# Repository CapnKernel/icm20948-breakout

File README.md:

# icm20948-breakout
A PCB done in KiCad to break out an ICM20948 IMU

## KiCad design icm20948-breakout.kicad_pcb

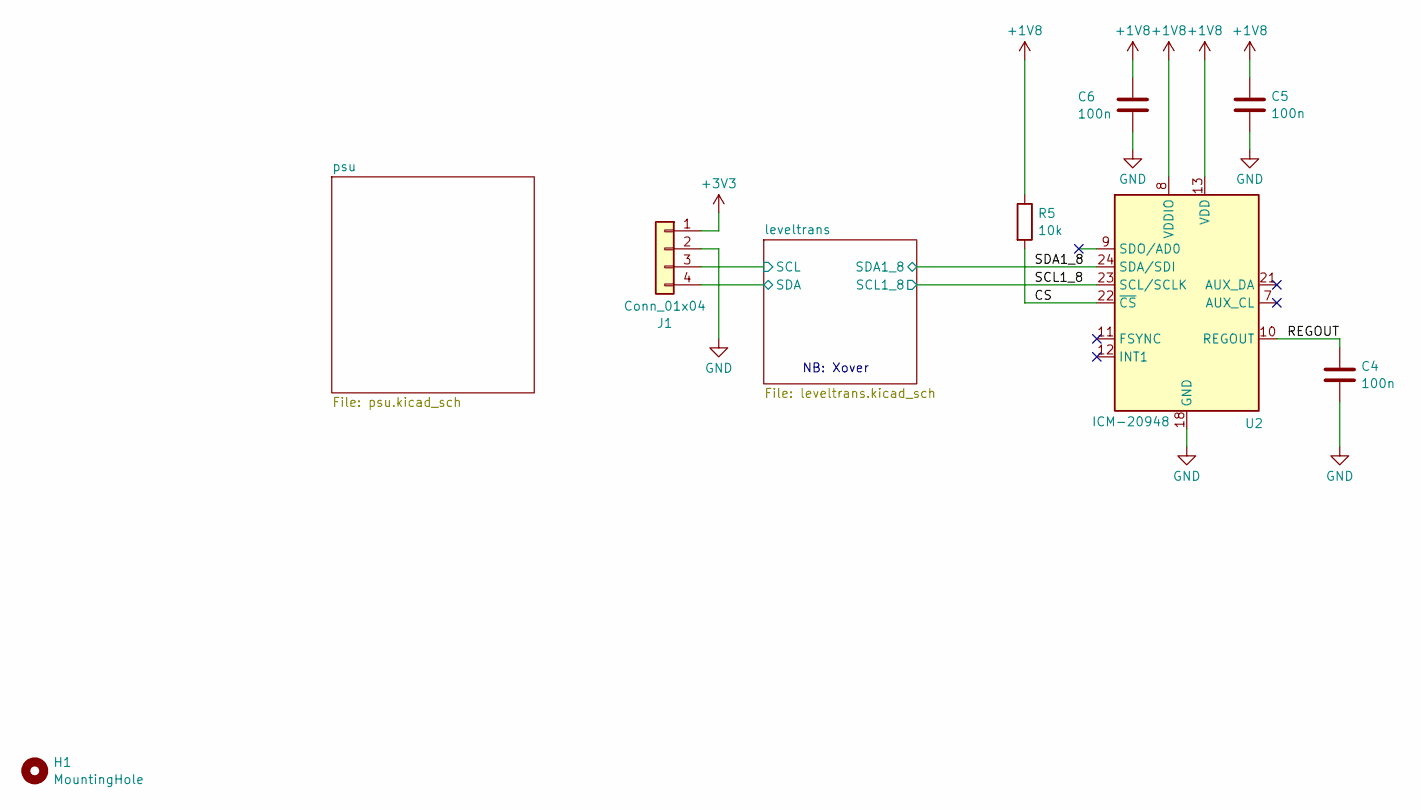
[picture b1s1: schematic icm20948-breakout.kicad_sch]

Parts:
C4, C5, C6: 100n; C_0402_1005Metric_Pad0.74x0.62mm_HandSolder; LCSC C1525
H1: MountingHole; MountingHole_2.2mm_M2
J1: Conn_01x04; PinHeader_1x04_P2.54mm_Vertical
R5: 10k; R_0402_1005Metric_Pad0.72x0.64mm_HandSolder; LCSC C25744
U2: ICM-20948; InvenSense_QFN-24_3x3mm_P0.4mm; LCSC C726001

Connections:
+1V8: C5.1, C6.1, R5.1, U2.8 (VDDIO), U2.13 (VDD); also elsewhere on the board
+3V3: J1.1; also elsewhere on the board
/CS: R5.2, U2.22 (~CS)
/REGOUT: C4.1, U2.10 (REGOUT)
/SCL1_8: U2.23 (SCL/SCLK); also elsewhere on the board
/SDA1_8: U2.24 (SDA/SDI); also elsewhere on the board
/leveltrans/SCL: J1.3; also elsewhere on the board
/leveltrans/SDA: J1.4; also elsewhere on the board
GND: C4.2, C5.2, C6.2, J1.2, U2.18 (GND), U2.20 (GND); also elsewhere on the board

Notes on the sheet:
NB: Xover

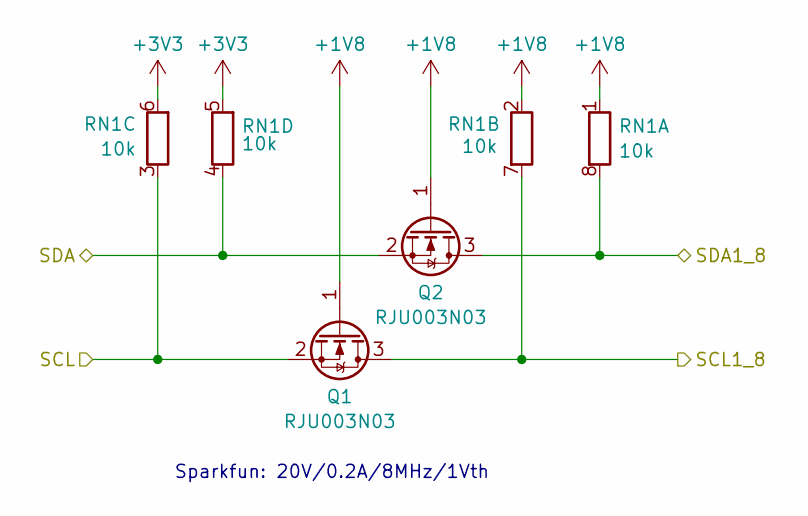
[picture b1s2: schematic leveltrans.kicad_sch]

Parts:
Q1, Q2: RJU003N03; SOT-323_SC-70_Handsoldering; LCSC C308741
RN1: 10k; R_Array_Convex_4x0603; LCSC C29718

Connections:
+1V8: Q1.1 (G), Q2.1 (G), RN1.1 (R1.1), RN1.2 (R2.1); also elsewhere on the board
+3V3: RN1.5 (R4.2), RN1.6 (R3.2); also elsewhere on the board
/SCL1_8: Q1.3 (D), RN1.7 (R2.2); also elsewhere on the board
/SDA1_8: Q2.3 (D), RN1.8 (R1.2); also elsewhere on the board
/leveltrans/SCL: Q1.2 (S), RN1.3 (R3.1); also elsewhere on the board
/leveltrans/SDA: Q2.2 (S), RN1.4 (R4.1); also elsewhere on the board

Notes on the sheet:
Sparkfun: 20V/0.2A/8MHz/1Vth

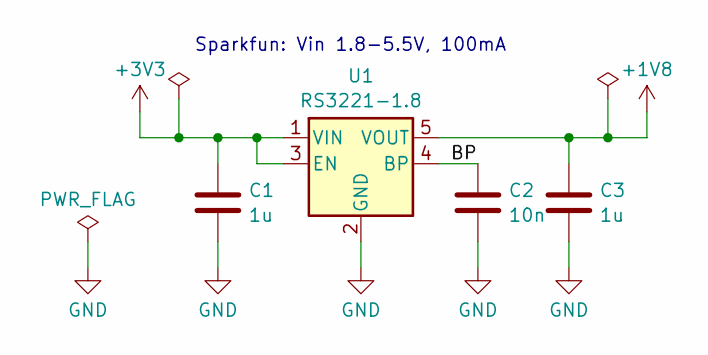
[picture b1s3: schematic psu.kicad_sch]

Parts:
C1, C3: 1u; C_0402_1005Metric_Pad0.74x0.62mm_HandSolder; LCSC C52923
C2: 10n; C_0402_1005Metric_Pad0.74x0.62mm_HandSolder; LCSC C15195
U1: RS3221-1.8; SOT-23-5; LCSC C2762317

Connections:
+1V8: C3.1, U1.5 (VOUT); also elsewhere on the board
+3V3: C1.1, U1.1 (VIN), U1.3 (EN); also elsewhere on the board
/psu/BP: C2.1, U1.4 (BP)
GND: C1.2, C2.2, C3.2, U1.2 (GND); also elsewhere on the board

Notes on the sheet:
Sparkfun: Vin 1.8-5.5V, 100mA

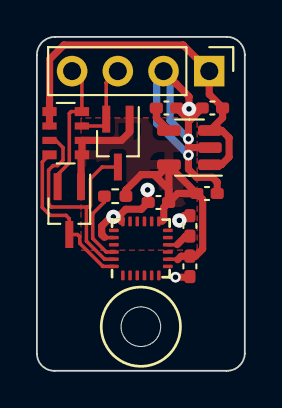
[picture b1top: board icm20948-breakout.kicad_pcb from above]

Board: 2 copper layers, 11.6 x 18.5 mm, 14 parts (0 on the bottom side), 10 nets.

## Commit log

2024-01-03 Extra things to ignore
2024-01-03 Empty KiCad project files.
2024-01-03 Rewrite using KiCad 8
2024-01-03 Set up local (empty) symbol and footprint libraries
2024-01-03 First cut of schematic
2024-01-03 1.0a
2024-01-03 Ignore output files.
2024-01-05 A whole bunch of changes after speaking with Jon.
2024-01-06 Changes for v1.1b
